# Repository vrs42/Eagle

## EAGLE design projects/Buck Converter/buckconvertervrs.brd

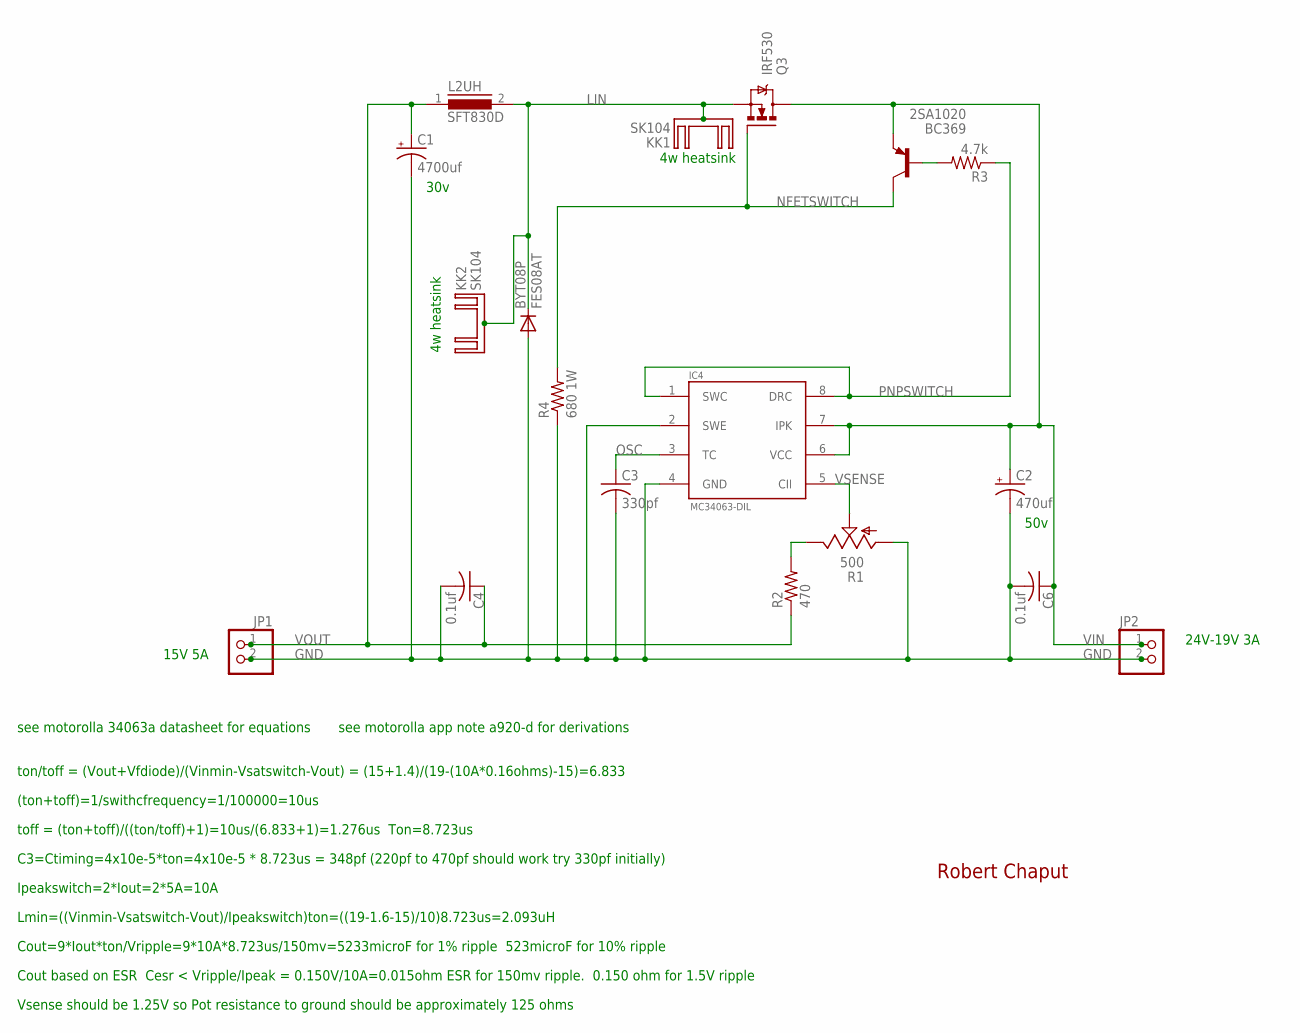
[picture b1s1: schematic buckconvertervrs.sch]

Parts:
2SA1020: BC369; TO92-BCE
BYT08P: FES08AT; DO220S
C1: 4700uf; EB30D
C2: 470uf; E5-8,5
C3: 330pf; C050-030X075
C4, C6: 0.1uf; C050-030X075
IC4: MC34063-DIL; DIL08
JP1, JP2: PINHD-1X2; 1X02
KK1, KK2: SK104
L2UH: SFT830D
Q3: IRF530; TO220BV
R1: 500; PT-SPIN
R2: 470; 0309V
R3: 4.7k; 0309V
R4: 680 1W; P0613V

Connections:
GND: BYT08P.A, C1.-, C2.-, C3.2, C4.2, C6.2, IC4.2 (SWE), IC4.4 (GND), JP1.2, JP2.2, R1.A, R4.1
LIN: BYT08P.C, L2UH.2, Q3.S
unnamed: R1.E, R2.2
unnamed: 2SA1020.B, R3.2
NFETSWITCH: 2SA1020.C, Q3.G, R4.2
OSC: C3.1, IC4.3 (TC)
PNPSWITCH: IC4.1 (SWC), IC4.8 (DRC), R3.1
VIN: 2SA1020.E, C2.+, C6.1, IC4.6 (VCC), IC4.7 (IPK), JP2.1, Q3.D
VOUT: C1.+, C4.1, JP1.1, L2UH.1, R2.1
VSENSE: IC4.5 (CII), R1.S

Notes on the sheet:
4w heatsink
24V-19V 3A
15V 5A
ton/toff = (Vout+Vfdiode)/(Vinmin-Vsatswitch-Vout) = (15+1.4)/(19-(10A*0.16ohms)-15)=6.833
(ton+toff)=1/swithcfrequency=1/100000=10us
toff = (ton+toff)/((ton/toff)+1)=10us/(6.833+1)=1.276us Ton=8.723us
C3=Ctiming=4x10e-5*ton=4x10e-5 * 8.723us = 348pf (220pf to 470pf should work try 330pf initially)
Ipeakswitch=2*Iout=2*5A=10A
Lmin=((Vinmin-Vsatswitch-Vout)/Ipeakswitch)ton=((19-1.6-15)/10)8.723us=2.093uH
see motorolla 34063a datasheet for equations
see motorolla app note a920-d for derivations
Cout=9*Iout*ton/Vripple=9*10A*8.723us/150mv=5233microF for 1% ripple 523microF for 10% ripple
Cout based on ESR Cesr < Vripple/Ipeak = 0.150V/10A=0.015ohm ESR for 150mv ripple. 0.150 ohm for 1.5V ripple
Vsense should be 1.25V so Pot resistance to ground should be approximately 125 ohms
50v
30v
Robert Chaput

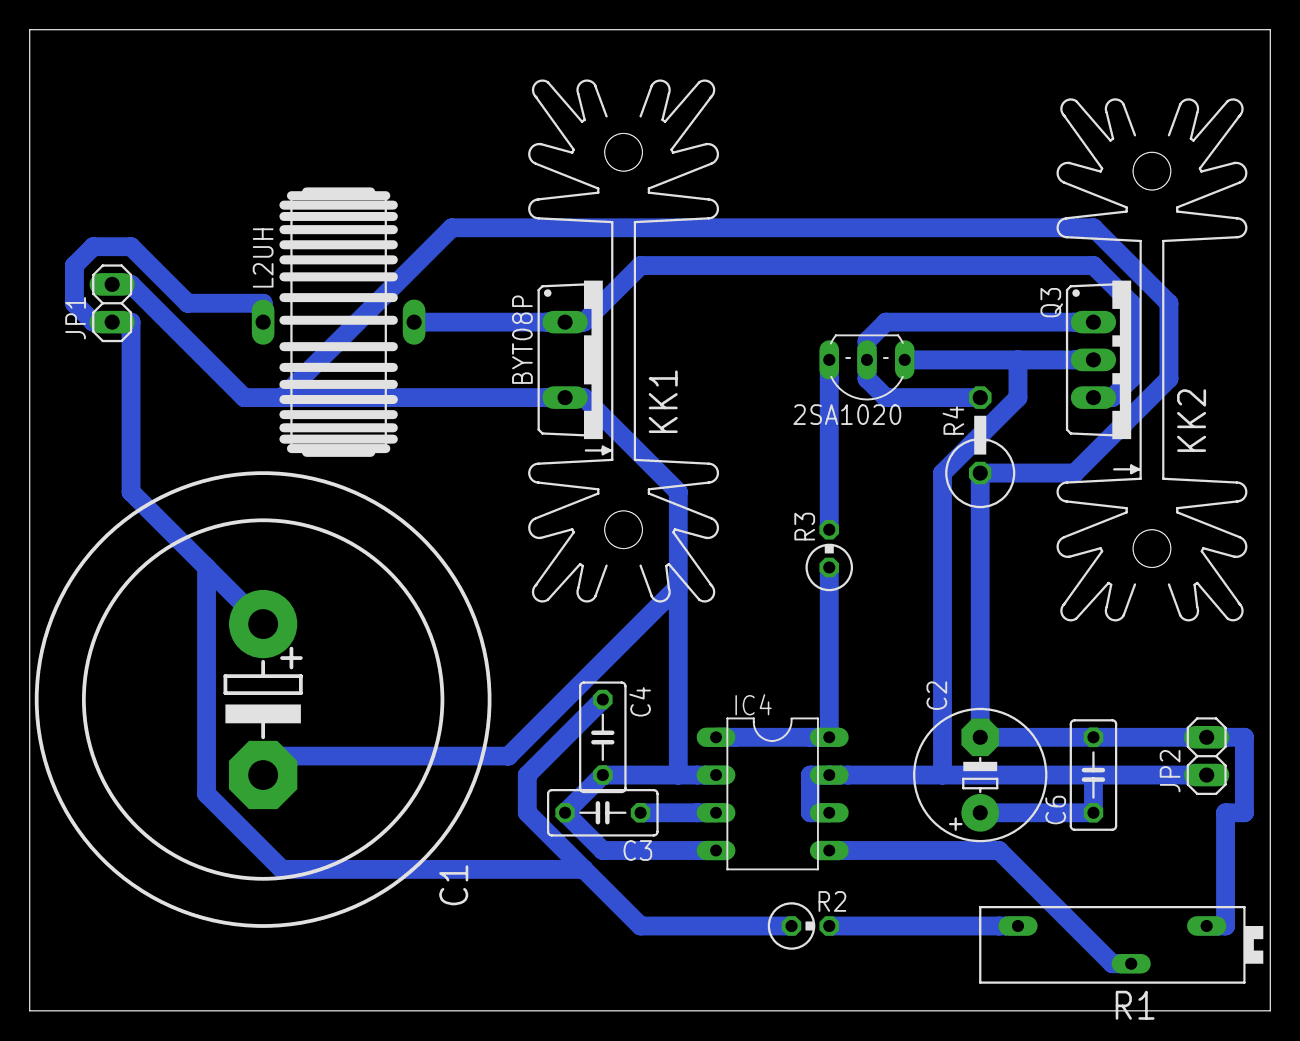
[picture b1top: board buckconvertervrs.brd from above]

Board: 2 copper layers, 83.5 x 66.0 mm, 18 parts (0 on the bottom side), 10 nets.

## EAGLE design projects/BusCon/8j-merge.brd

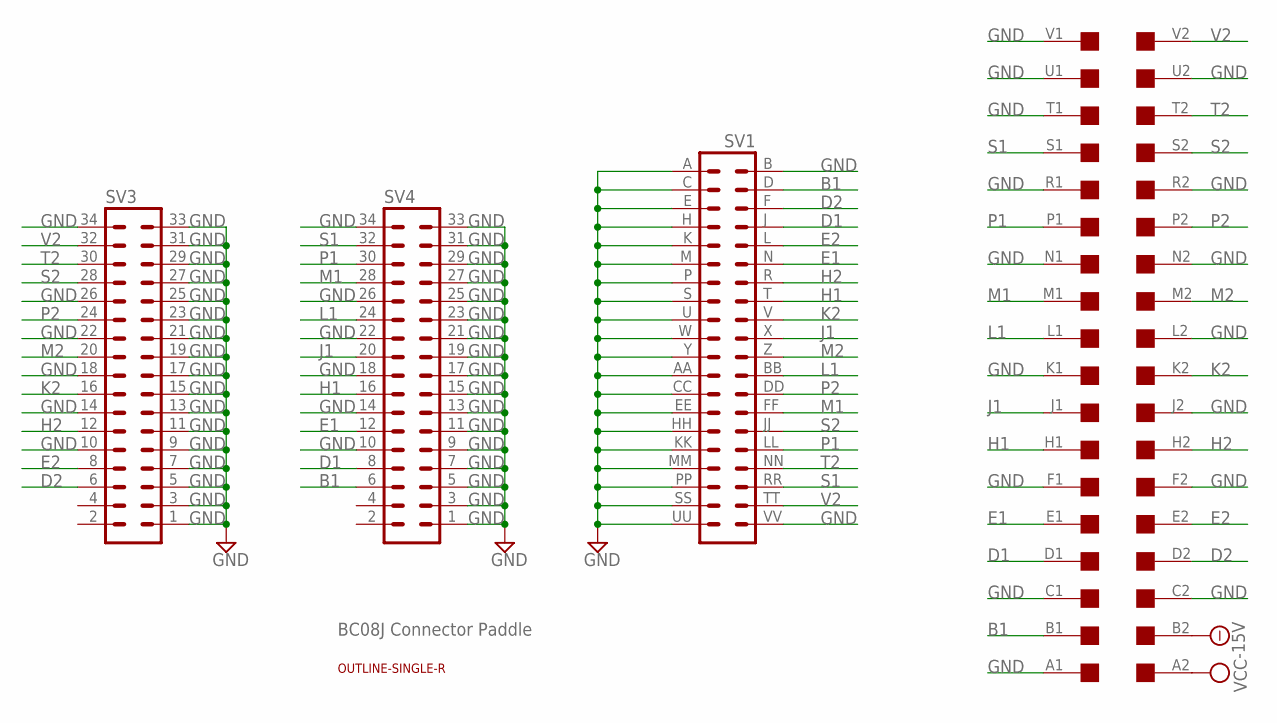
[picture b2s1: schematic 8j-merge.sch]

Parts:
SV1: DEC40PINV
SV3, SV4: MA17-2
U$1: OUTLINE-SINGLE-R; SINGLE-R
U$2: SINGLE; EDGE-CON2

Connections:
-15V: U$2.B2
B1: SV1.D (4), SV4.6, U$2.B1
D1: SV1.J (8), SV4.8, U$2.D1
D2: SV1.F (6), SV3.6, U$2.D2
E1: SV1.N (12), SV4.12, U$2.E1
E2: SV1.L (10), SV3.8, U$2.E2
GND: SV1.A (1), SV1.AA (23), SV1.B (2), SV1.C (3), SV1.CC (25), SV1.E (5), SV1.EE (27), SV1.H (7), SV1.HH (29), SV1.K (9), SV1.KK (31), SV1.M (11), SV1.MM (33), SV1.P (13), SV1.PP (35), SV1.S (15), SV1.SS (37), SV1.U (17), SV1.UU (39), SV1.VV (40), SV1.W (19), SV1.Y (21), SV3.1, SV3.3, SV3.5, SV3.7, SV3.9, SV3.10, SV3.11, SV3.13, SV3.14, SV3.15, SV3.17, SV3.18, SV3.19, SV3.21, SV3.22, SV3.23, SV3.25, SV3.26, SV3.27, SV3.29, SV3.31, SV3.33, SV3.34, SV4.1, SV4.3, SV4.5, SV4.7, SV4.9, SV4.10, SV4.11, SV4.13, SV4.14, SV4.15, SV4.17, SV4.18, SV4.19, SV4.21, SV4.22, SV4.23, SV4.25, SV4.26, SV4.27, SV4.29, SV4.31, SV4.33, SV4.34, U$2.A1, U$2.C1, U$2.C2, U$2.F1, U$2.F2, U$2.J2, U$2.K1, U$2.L2, U$2.N1, U$2.N2, U$2.R1, U$2.R2, U$2.T1, U$2.U1, U$2.U2, U$2.V1
H1: SV1.T (16), SV4.16, U$2.H1
H2: SV1.R (14), SV3.12, U$2.H2
J1: SV1.X (20), SV4.20, U$2.J1
K2: SV1.V (18), SV3.16, U$2.K2
L1: SV1.BB (24), SV4.24, U$2.L1
M1: SV1.FF (28), SV4.28, U$2.M1
M2: SV1.Z (22), SV3.20, U$2.M2
P1: SV1.LL (32), SV4.30, U$2.P1
P2: SV1.DD (26), SV3.24, U$2.P2
S1: SV1.RR (36), SV4.32, U$2.S1
S2: SV1.JJ (30), SV3.28, U$2.S2
T2: SV1.NN (34), SV3.30, U$2.T2
V2: SV1.TT (38), SV3.32, U$2.V2
VCC: U$2.A2

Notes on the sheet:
BC08J Connector Paddle

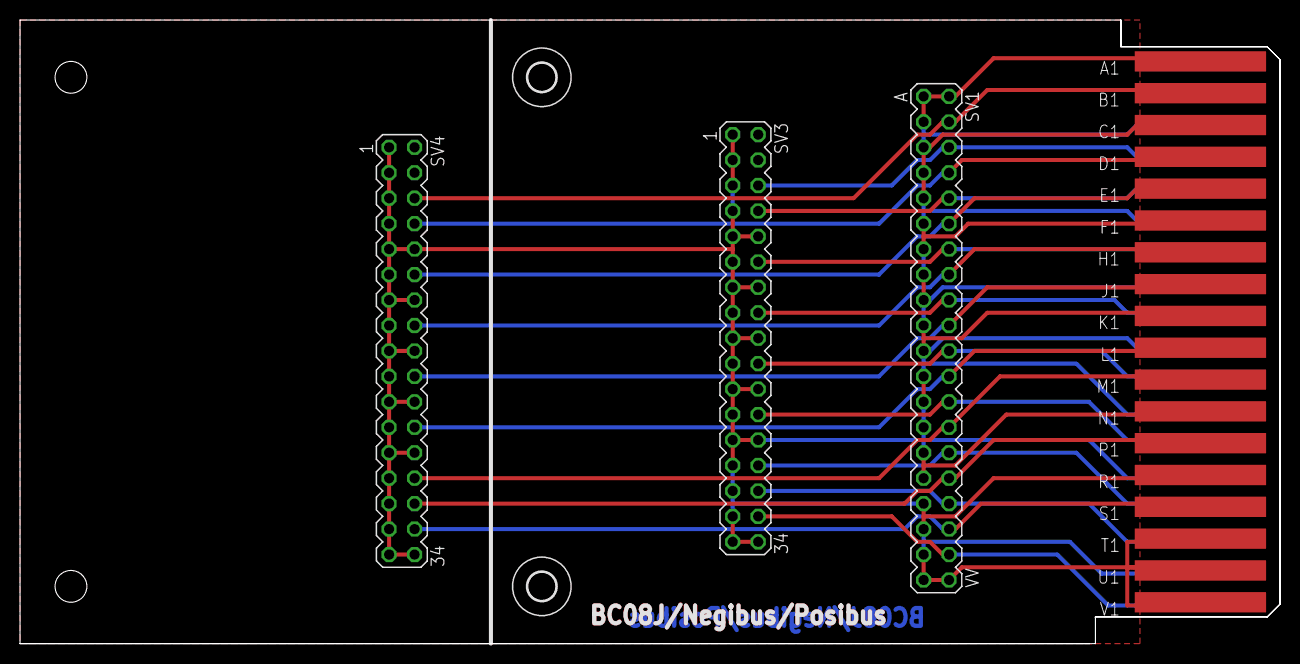
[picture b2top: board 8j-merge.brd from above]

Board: 2 copper layers, 125.7 x 62.2 mm, 7 parts (0 on the bottom side), 19 nets.

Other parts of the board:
U$3, U$4: 2,8

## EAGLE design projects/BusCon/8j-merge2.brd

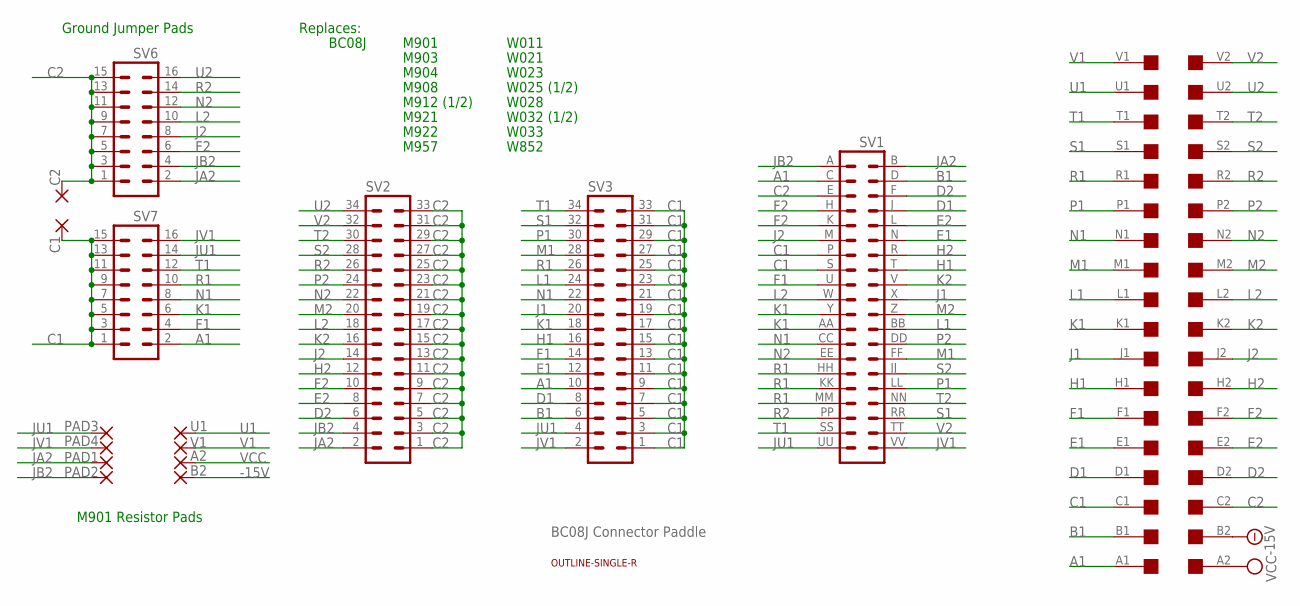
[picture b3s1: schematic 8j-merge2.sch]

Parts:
A2: 1,6/0,8
B2: 1,6/0,8
C1, C2: 1,6/0,8
PAD1, PAD2, PAD3, PAD4: 1,6/0,8
SV1: DEC40PINV
SV2, SV3: MA17-2
SV6, SV7: MA08-2
U1: 1,6/0,8
U$1: OUTLINE-SINGLE-R; SINGLE-R
U$2: SINGLE; EDGE-CON2
V1: 1,6/0,8

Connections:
-15V: B2.1, U$2.B2
A1: SV1.C (3), SV3.10, SV7.2, U$2.A1
B1: SV1.D (4), SV3.6, U$2.B1
C1: C1.1, SV1.P (13), SV1.S (15), SV3.1, SV3.3, SV3.5, SV3.7, SV3.9, SV3.11, SV3.13, SV3.15, SV3.17, SV3.19, SV3.21, SV3.23, SV3.25, SV3.27, SV3.29, SV3.31, SV3.33, SV7.1, SV7.3, SV7.5, SV7.7, SV7.9, SV7.11, SV7.13, SV7.15, U$2.C1
C2: C2.1, SV1.E (5), SV2.1, SV2.3, SV2.5, SV2.7, SV2.9, SV2.11, SV2.13, SV2.15, SV2.17, SV2.19, SV2.21, SV2.23, SV2.25, SV2.27, SV2.29, SV2.31, SV2.33, SV6.1, SV6.3, SV6.5, SV6.7, SV6.9, SV6.11, SV6.13, SV6.15, U$2.C2
D1: SV1.J (8), SV3.8, U$2.D1
D2: SV1.F (6), SV2.6, U$2.D2
E1: SV1.N (12), SV3.12, U$2.E1
E2: SV1.L (10), SV2.8, U$2.E2
F1: SV1.U (17), SV3.14, SV7.4, U$2.F1
F2: SV1.H (7), SV1.K (9), SV2.10, SV6.6, U$2.F2
H1: SV1.T (16), SV3.16, U$2.H1
H2: SV1.R (14), SV2.12, U$2.H2
J1: SV1.X (20), SV3.20, U$2.J1
J2: SV1.M (11), SV2.14, SV6.8, U$2.J2
JA2: PAD1.1, SV1.B (2), SV2.2, SV6.2
JB2: PAD2.1, SV1.A (1), SV2.4, SV6.4
JU1: PAD3.1, SV1.UU (39), SV3.4, SV7.14
JV1: PAD4.1, SV1.VV (40), SV3.2, SV7.16
K1: SV1.AA (23), SV1.Y (21), SV3.18, SV7.6, U$2.K1
K2: SV1.V (18), SV2.16, U$2.K2
L1: SV1.BB (24), SV3.24, U$2.L1
L2: SV1.W (19), SV2.18, SV6.10, U$2.L2
M1: SV1.FF (28), SV3.28, U$2.M1
M2: SV1.Z (22), SV2.20, U$2.M2
N1: SV1.CC (25), SV3.22, SV7.8, U$2.N1
N2: SV1.EE (27), SV2.22, SV6.12, U$2.N2
P1: SV1.LL (32), SV3.30, U$2.P1
P2: SV1.DD (26), SV2.24, U$2.P2
R1: SV1.HH (29), SV1.KK (31), SV1.MM (33), SV3.26, SV7.10, U$2.R1
R2: SV1.PP (35), SV2.26, SV6.14, U$2.R2
S1: SV1.RR (36), SV3.32, U$2.S1
S2: SV1.JJ (30), SV2.28, U$2.S2
T1: SV1.SS (37), SV3.34, SV7.12, U$2.T1
T2: SV1.NN (34), SV2.30, U$2.T2
U1: U1.1, U$2.U1
U2: SV2.34, SV6.16, U$2.U2
V1: U$2.V1, V1.1
V2: SV1.TT (38), SV2.32, U$2.V2
VCC: A2.1, U$2.A2

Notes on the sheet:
BC08J Connector Paddle
M901 Resistor Pads
Ground Jumper Pads
Replaces:
M901
M903
M904
M908
M912 (1/2)
M921
M922
M957
W011
W021
W023
W025 (1/2)
W028
W032 (1/2)
W033
W852
BC08J

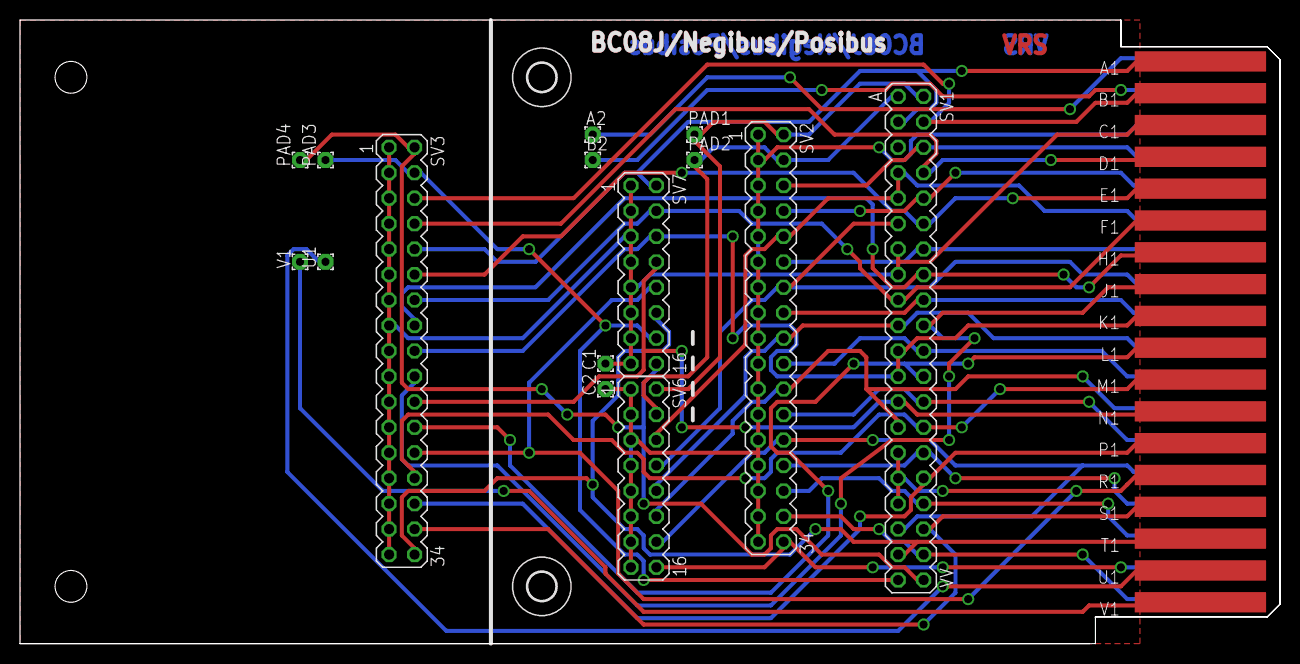
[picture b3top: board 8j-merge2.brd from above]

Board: 2 copper layers, 125.7 x 62.2 mm, 19 parts (0 on the bottom side), 40 nets.

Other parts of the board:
U$3, U$4: 2,8

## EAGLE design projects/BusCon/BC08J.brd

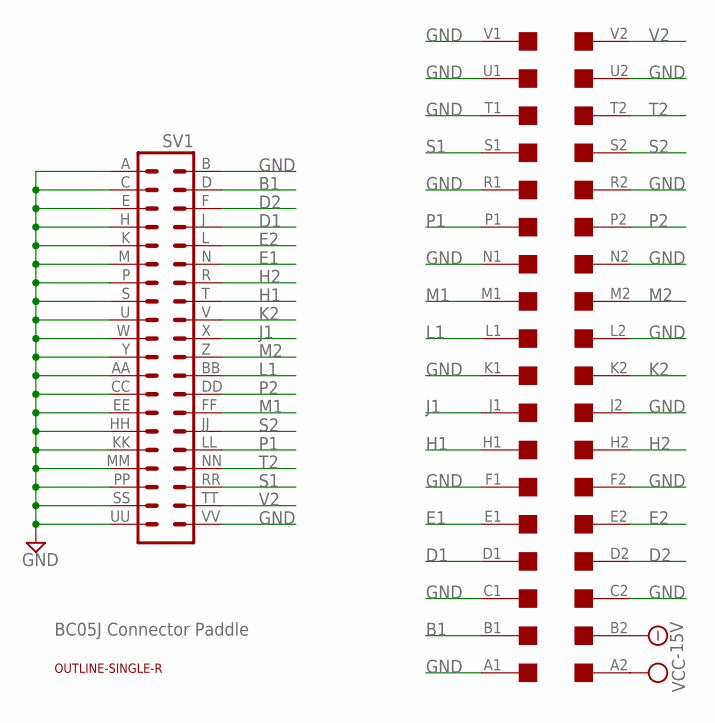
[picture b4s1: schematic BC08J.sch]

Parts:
SV1: DEC40PINV
U$1: SINGLE; EDGE-CON2
U$2: OUTLINE-SINGLE-R; SINGLE-R

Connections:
-15V: U$1.B2
B1: SV1.D (4), U$1.B1
D1: SV1.J (8), U$1.D1
D2: SV1.F (6), U$1.D2
E1: SV1.N (12), U$1.E1
E2: SV1.L (10), U$1.E2
GND: SV1.A (1), SV1.AA (23), SV1.B (2), SV1.C (3), SV1.CC (25), SV1.E (5), SV1.EE (27), SV1.H (7), SV1.HH (29), SV1.K (9), SV1.KK (31), SV1.M (11), SV1.MM (33), SV1.P (13), SV1.PP (35), SV1.S (15), SV1.SS (37), SV1.U (17), SV1.UU (39), SV1.VV (40), SV1.W (19), SV1.Y (21), U$1.A1, U$1.C1, U$1.C2, U$1.F1, U$1.F2, U$1.J2, U$1.K1, U$1.L2, U$1.N1, U$1.N2, U$1.R1, U$1.R2, U$1.T1, U$1.U1, U$1.U2, U$1.V1
H1: SV1.T (16), U$1.H1
H2: SV1.R (14), U$1.H2
J1: SV1.X (20), U$1.J1
K2: SV1.V (18), U$1.K2
L1: SV1.BB (24), U$1.L1
M1: SV1.FF (28), U$1.M1
M2: SV1.Z (22), U$1.M2
P1: SV1.LL (32), U$1.P1
P2: SV1.DD (26), U$1.P2
S1: SV1.RR (36), U$1.S1
S2: SV1.JJ (30), U$1.S2
T2: SV1.NN (34), U$1.T2
V2: SV1.TT (38), U$1.V2
VCC: U$1.A2

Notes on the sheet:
BC05J Connector Paddle

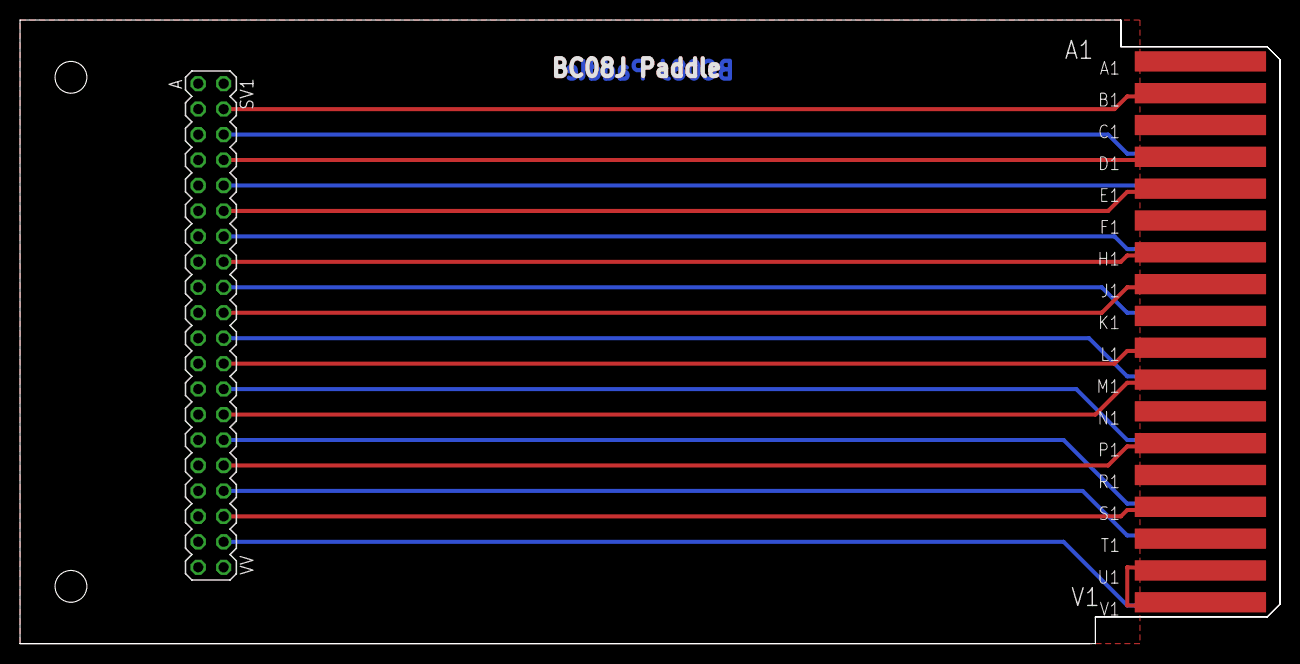
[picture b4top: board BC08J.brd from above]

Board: 2 copper layers, 125.7 x 62.2 mm, 3 parts (0 on the bottom side), 19 nets.

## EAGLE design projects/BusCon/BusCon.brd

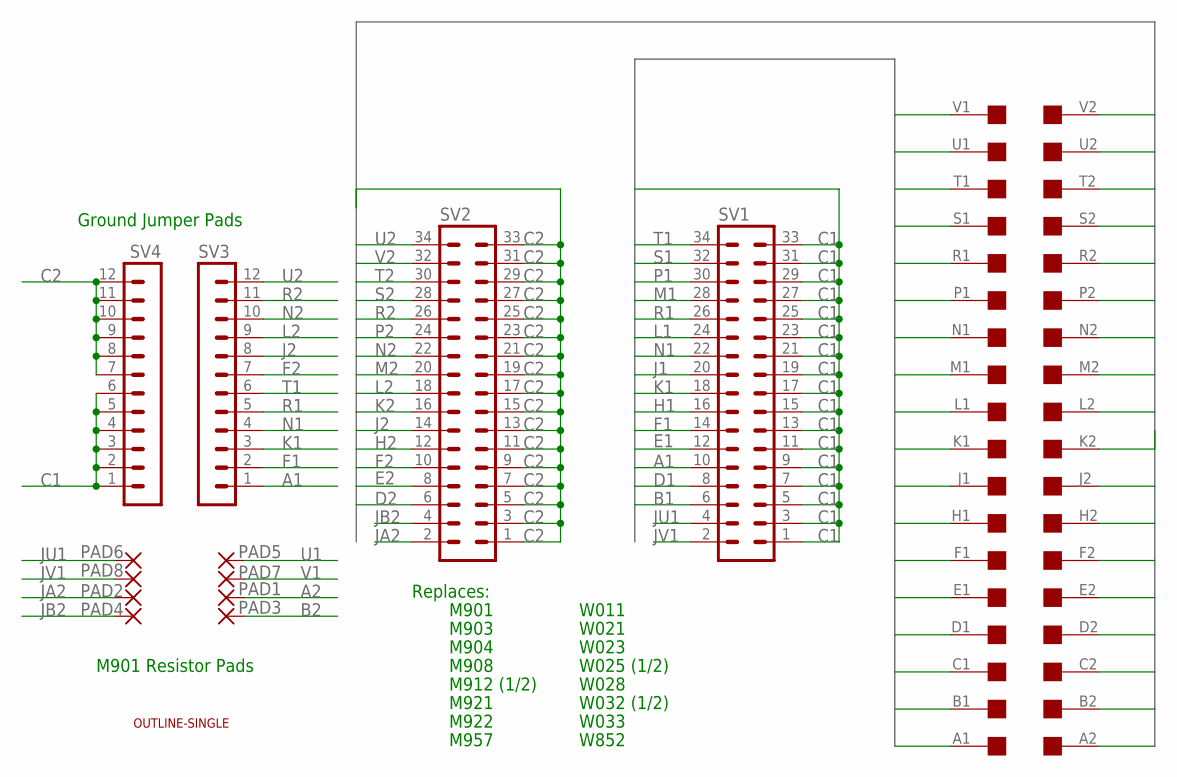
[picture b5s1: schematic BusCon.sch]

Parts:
PAD1, PAD2, PAD3, PAD4, PAD5, PAD6, PAD7, PAD8: 1,6/0,8
SV1, SV2: MA17-2
SV3, SV4: MA12-1
U$1: OUTLINE-SINGLE; SINGLE
U$4: EDGE-2CONNECTOR; EDGE-CON2

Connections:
A1: SV1.10, SV3.1, U$4.A1
A2: PAD1.1, U$4.A2
B1: SV1.6, U$4.B1
B2: PAD3.1, U$4.B2
C1: SV1.1, SV1.3, SV1.5, SV1.7, SV1.9, SV1.11, SV1.13, SV1.15, SV1.17, SV1.19, SV1.21, SV1.23, SV1.25, SV1.27, SV1.29, SV1.31, SV1.33, SV4.1, SV4.2, SV4.3, SV4.4, SV4.5, SV4.6, U$4.C1
C2: SV2.1, SV2.3, SV2.5, SV2.7, SV2.9, SV2.11, SV2.13, SV2.15, SV2.17, SV2.19, SV2.21, SV2.23, SV2.25, SV2.27, SV2.29, SV2.31, SV2.33, SV4.7, SV4.8, SV4.9, SV4.10, SV4.11, SV4.12, U$4.C2
D1: SV1.8, U$4.D1
D2: SV2.6, U$4.D2
E1: SV1.12, U$4.E1
E2: SV2.8, U$4.E2
F1: SV1.14, SV3.2, U$4.F1
F2: SV2.10, SV3.7, U$4.F2
H1: SV1.16, U$4.H1
H2: SV2.12, U$4.H2
J1: SV1.20, U$4.J1
J2: SV2.14, SV3.8, U$4.J2
JA2: PAD2.1, SV2.2
JB2: PAD4.1, SV2.4
JU1: PAD6.1, SV1.4
JV1: PAD8.1, SV1.2
K1: SV1.18, SV3.3, U$4.K1
K2: SV2.16, U$4.K2
L1: SV1.24, U$4.L1
L2: SV2.18, SV3.9, U$4.L2
M1: SV1.28, U$4.M1
M2: SV2.20, U$4.M2
N1: SV1.22, SV3.4, U$4.N1
N2: SV2.22, SV3.10, U$4.N2
P1: SV1.30, U$4.P1
P2: SV2.24, U$4.P2
R1: SV1.26, SV3.5, U$4.R1
R2: SV2.26, SV3.11, U$4.R2
S1: SV1.32, U$4.S1
S2: SV2.28, U$4.S2
T1: SV1.34, SV3.6, U$4.T1
T2: SV2.30, U$4.T2
U1: PAD5.1, U$4.U1
U2: SV2.34, SV3.12, U$4.U2
V1: PAD7.1, U$4.V1
V2: SV2.32, U$4.V2

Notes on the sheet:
M901 Resistor Pads
Ground Jumper Pads
Replaces:
M901
M903
M904
M908
M912 (1/2)
M921
M922
M957
W011
W021
W023
W025 (1/2)
W028
W032 (1/2)
W033
W852

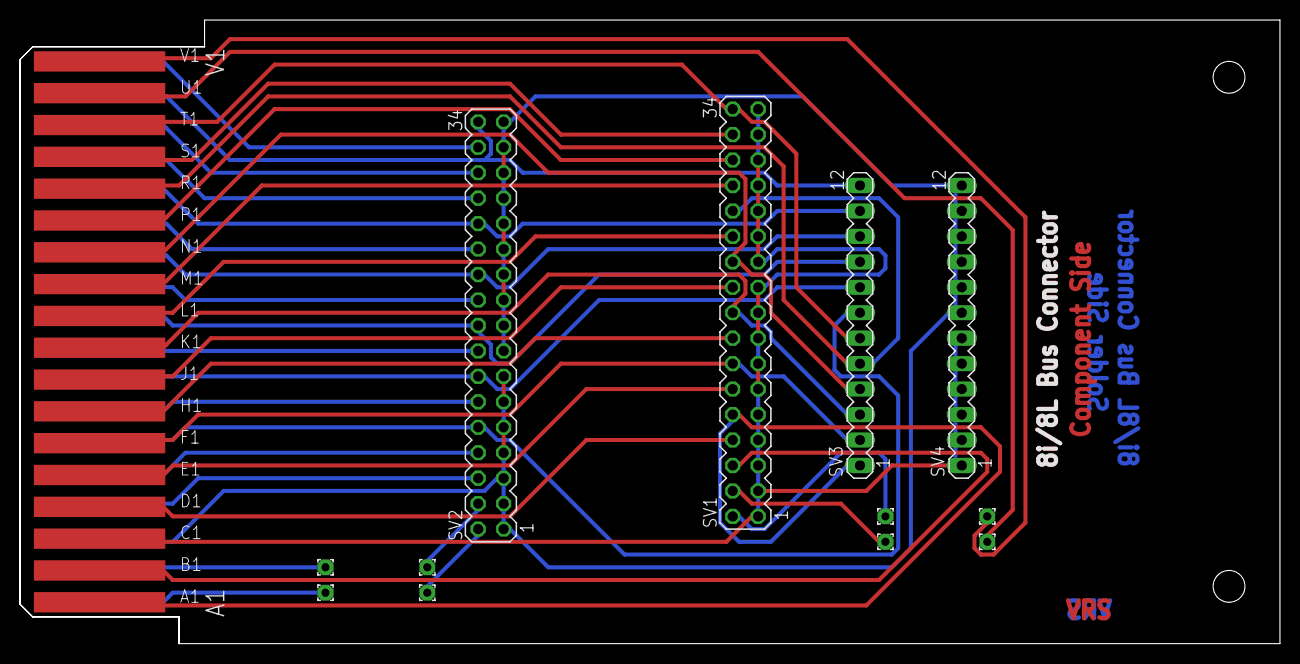
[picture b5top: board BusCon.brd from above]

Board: 2 copper layers, 125.7 x 62.2 mm, 14 parts (0 on the bottom side), 40 nets.

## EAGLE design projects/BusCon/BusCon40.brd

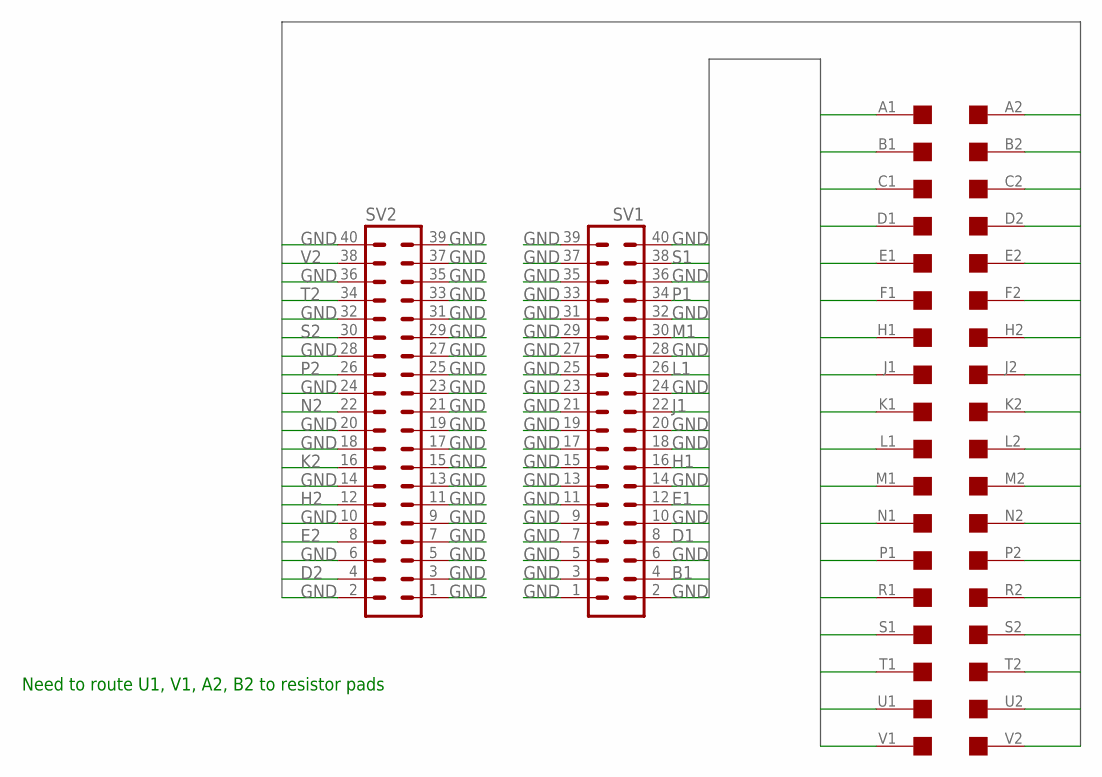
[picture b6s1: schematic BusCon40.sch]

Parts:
SV1, SV2: MA20-2W
U$1: DEC-FLIPCHIP

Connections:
A2: U$1.A2
B1: SV1.4, U$1.B1
B2: U$1.B2
D1: SV1.8, U$1.D1
D2: SV2.4, U$1.D2
E1: SV1.12, U$1.E1
E2: SV2.8, U$1.E2
GND: SV1.1, SV1.2, SV1.3, SV1.5, SV1.6, SV1.7, SV1.9, SV1.10, SV1.11, SV1.13, SV1.14, SV1.15, SV1.17, SV1.18, SV1.19, SV1.20, SV1.21, SV1.23, SV1.24, SV1.25, SV1.27, SV1.28, SV1.29, SV1.31, SV1.32, SV1.33, SV1.35, SV1.36, SV1.37, SV1.39, SV1.40, SV2.1, SV2.2, SV2.3, SV2.5, SV2.6, SV2.7, SV2.9, SV2.10, SV2.11, SV2.13, SV2.14, SV2.15, SV2.17, SV2.18, SV2.19, SV2.20, SV2.21, SV2.23, SV2.24, SV2.25, SV2.27, SV2.28, SV2.29, SV2.31, SV2.32, SV2.33, SV2.35, SV2.36, SV2.37, SV2.39, SV2.40, U$1.A1, U$1.C1, U$1.C2, U$1.F1, U$1.F2, U$1.J2, U$1.K1, U$1.L2, U$1.M2, U$1.N1, U$1.R1, U$1.R2, U$1.T1, U$1.U2
H1: SV1.16, U$1.H1
H2: SV2.12, U$1.H2
J1: SV1.22, U$1.J1
K2: SV2.16, U$1.K2
L1: SV1.26, U$1.L1
M1: SV1.30, U$1.M1
N2: SV2.22, U$1.N2
P1: SV1.34, U$1.P1
P2: SV2.26, U$1.P2
S1: SV1.38, U$1.S1
S2: SV2.30, U$1.S2
T2: SV2.34, U$1.T2
U1: U$1.U1
V1: U$1.V1
V2: SV2.38, U$1.V2

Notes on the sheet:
Need to route U1, V1, A2, B2 to resistor pads

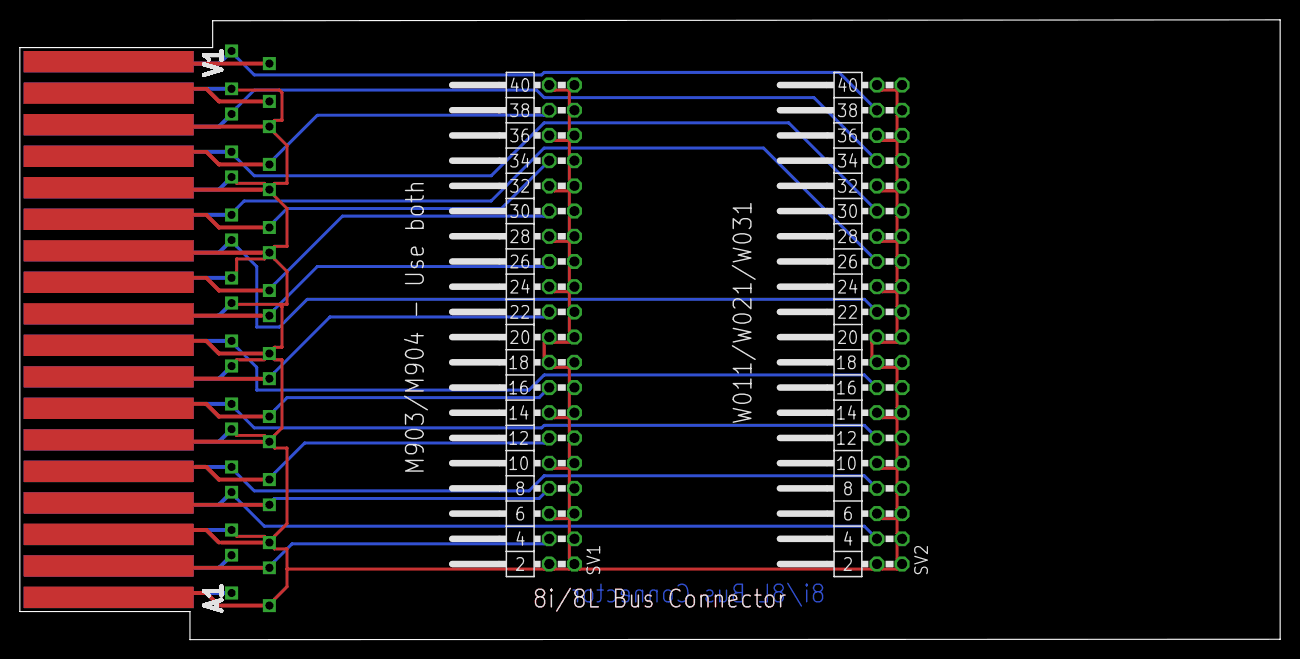
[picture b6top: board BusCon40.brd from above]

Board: 2 copper layers, 127.0 x 62.4 mm, 3 parts (0 on the bottom side), 19 nets.
